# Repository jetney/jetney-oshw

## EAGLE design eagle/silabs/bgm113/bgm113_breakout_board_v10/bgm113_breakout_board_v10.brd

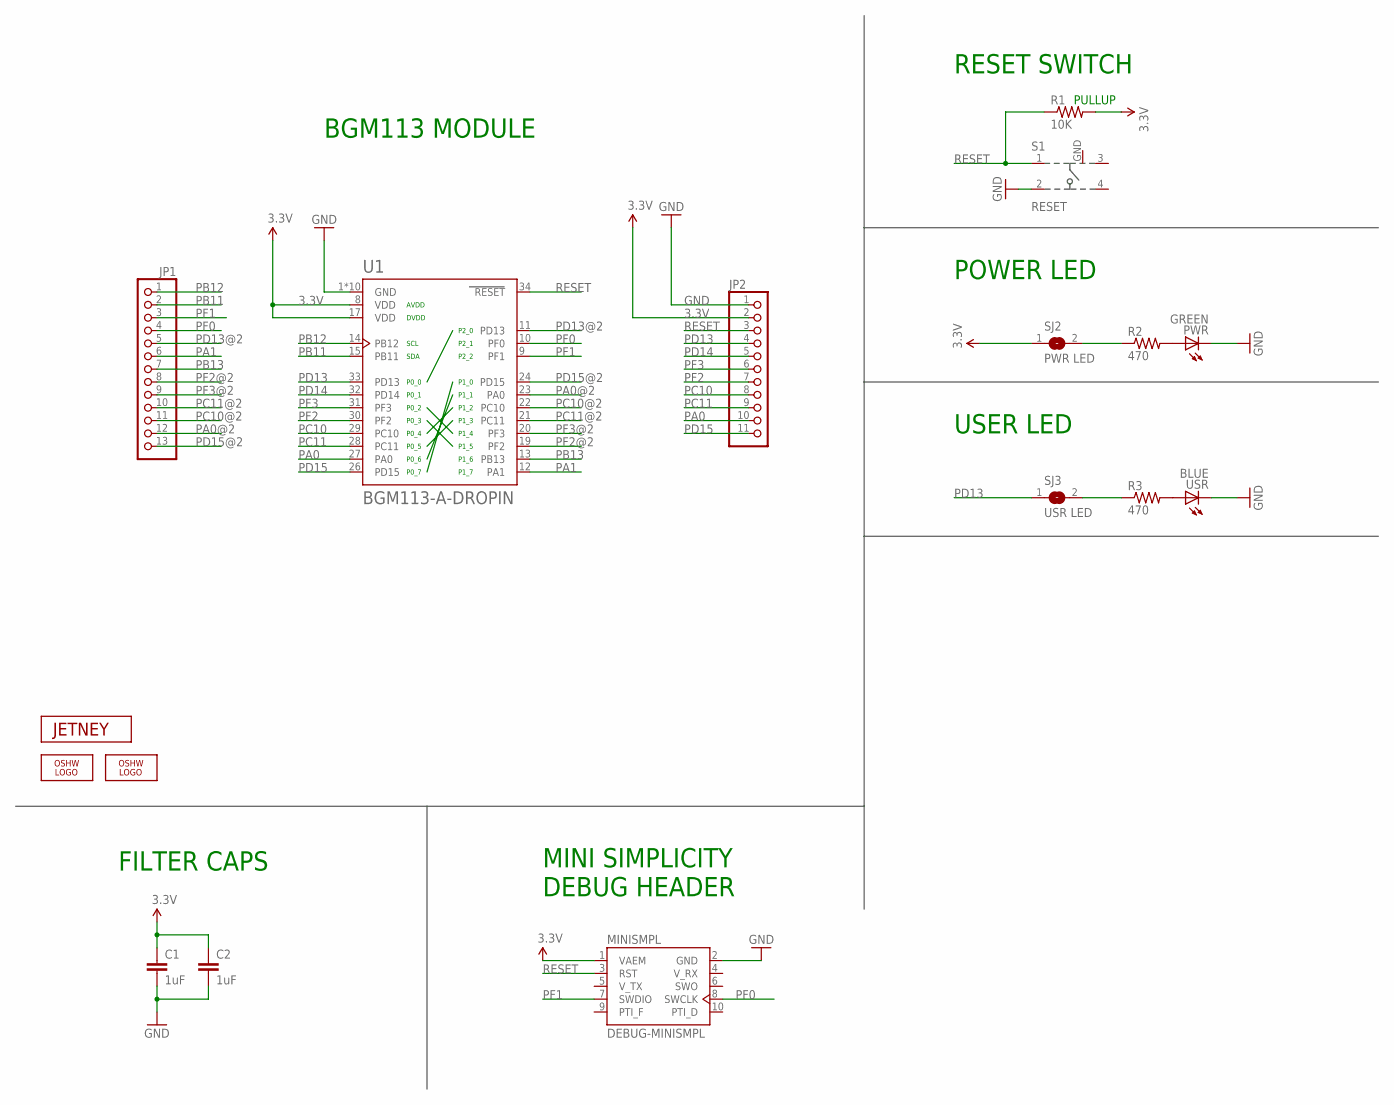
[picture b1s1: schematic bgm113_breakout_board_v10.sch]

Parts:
C1, C2: 1uF; 0603-CAP
JP1: PINHD-1X13; 1X13
JP2: PINHD-1X11; 1X11
LOGO1: OSHW_LOGO_FILLX0100-NT; OSHW_FILLX100_NOTEXT
LOGO2: OSHW_LOGO_FILLX0070-NT; OSHW_FILLX70_NOTEXT
MINISMPL: DEBUG-MINISMPL; DEBUG-50MIL
PWR: GREEN; CHIPLED_0805
R1: 10K; 0603-RES
R2, R3: 470; R0603
S1: RESET; 101-IG
SJ2: PWR LED; SJ
SJ3: USR LED; SJ
U1: BGM113-A-DROPIN; BLE113-A
U$2: JETNEY-LOGO-12
USR: BLUE; CHIPLED_0805

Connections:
3.3V: C1.1, C2.1, JP2.2, MINISMPL.1 (VAEM), R1.2, SJ2.1, U1.8 (VDD), U1.17 (VDD)
GND: C1.2, C2.2, JP2.1, MINISMPL.2 (GND), PWR.C, S1.2, S1.GND, U1.1 (GND), U1.2 (GND), U1.3 (GND), U1.4 (GND), U1.5 (GND), U1.6 (GND), U1.7 (GND), U1.18 (GND), U1.25 (GND), U1.36 (GND), USR.C
unnamed: PWR.A, R2.2
unnamed: R2.1, SJ2.2
unnamed: R3.2, USR.A
unnamed: R3.1, SJ3.2
PA0: JP2.10, U1.27 (PA0)
PA0@2: JP1.12, U1.23 (PA0)
PA1: JP1.6, U1.12 (PA1)
PB11: JP1.2, U1.15 (PB11)
PB12: JP1.1, U1.14 (PB12)
PB13: JP1.7, U1.13 (PB13)
PC10: JP2.8, U1.29 (PC10)
PC10@2: JP1.11, U1.22 (PC10)
PC11: JP2.9, U1.28 (PC11)
PC11@2: JP1.10, U1.21 (PC11)
PD13: JP2.4, SJ3.1, U1.33 (PD13)
PD13@2: JP1.5, U1.11 (PD13)
PD14: JP2.5, U1.32 (PD14)
PD15: JP2.11, U1.26 (PD15)
PD15@2: JP1.13, U1.24 (PD15)
PF0: JP1.4, MINISMPL.8 (SWCLK), U1.10 (PF0)
PF1: JP1.3, MINISMPL.7 (SWDIO), U1.9 (PF1)
PF2: JP2.7, U1.30 (PF2)
PF2@2: JP1.8, U1.19 (PF2)
PF3: JP2.6, U1.31 (PF3)
PF3@2: JP1.9, U1.20 (PF3)
RESET: JP2.3, MINISMPL.3 (RST), R1.1, S1.1, U1.34 (RESET)

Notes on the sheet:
POWER LED
USER LED
MINI SIMPLICITY DEBUG HEADER
BGM113 MODULE
RESET SWITCH
PULLUP
FILTER CAPS

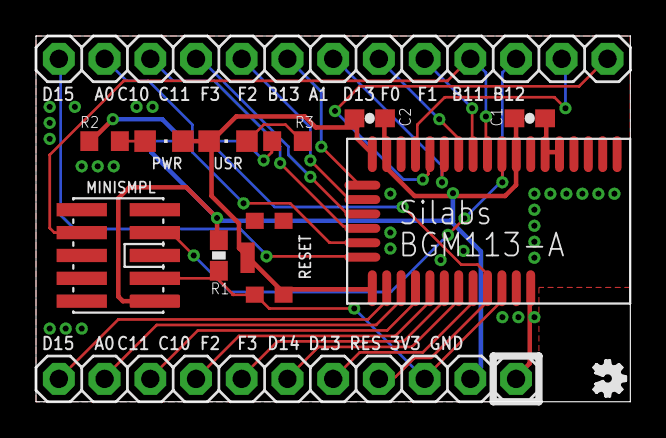
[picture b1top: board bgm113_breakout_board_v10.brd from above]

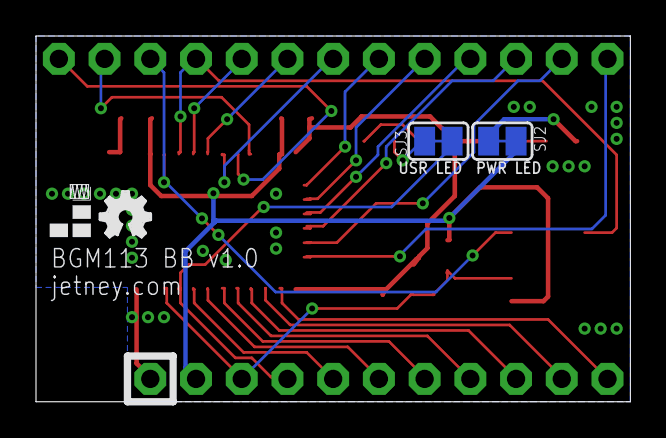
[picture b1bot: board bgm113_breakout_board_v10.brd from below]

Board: 2 copper layers, 33.0 x 20.3 mm, 17 parts (4 on the bottom side), 28 nets.

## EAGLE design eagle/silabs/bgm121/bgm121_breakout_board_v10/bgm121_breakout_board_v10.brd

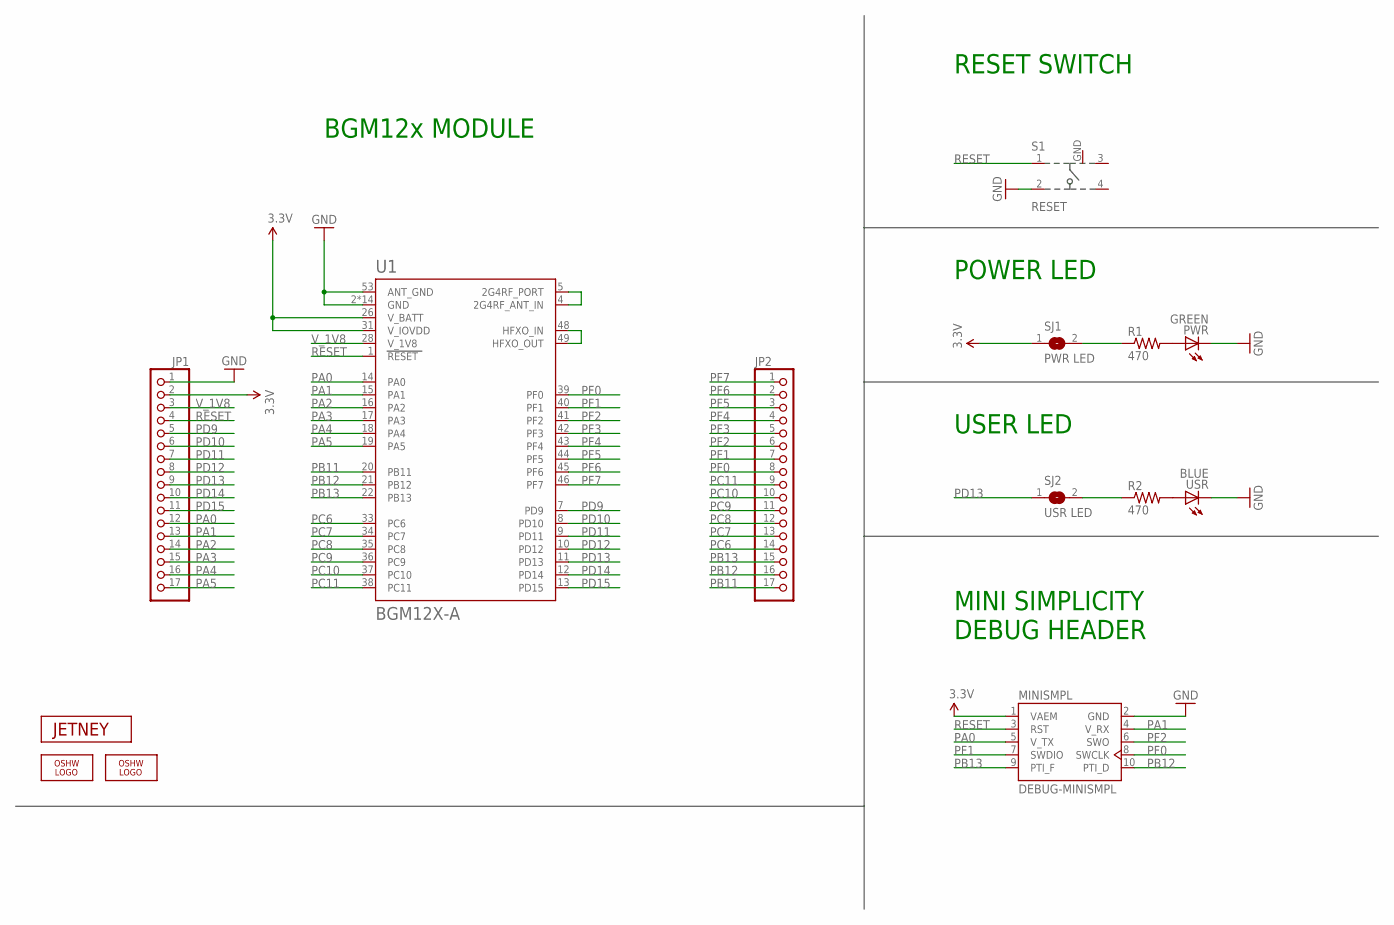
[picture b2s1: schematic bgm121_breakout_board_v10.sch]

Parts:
JP1, JP2: PINHD-1X17; 1X17
LOGO1: OSHW_LOGO_FILLX0100-NT; OSHW_FILLX100_NOTEXT
LOGO2: OSHW_LOGO_FILLX0070-NT; OSHW_FILLX70_NOTEXT
MINISMPL: DEBUG-MINISMPL; DEBUG-50MIL
PWR: GREEN; CHIPLED_0805
R1, R2: 470; R0603
S1: RESET; 101-IG
SJ1: PWR LED; SJ
SJ2: USR LED; SJ
U1: BGM12X-A
U$2: JETNEY-LOGO-12
USR: BLUE; CHIPLED_0805

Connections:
2G4RF: U1.4 (2G4RF_ANT_IN), U1.5 (2G4RF_PORT)
3.3V: JP1.2, MINISMPL.1 (VAEM), SJ1.1, U1.26 (V_BATT), U1.31 (V_IOVDD)
GND: JP1.1, MINISMPL.2 (GND), PWR.C, S1.2, S1.GND, U1.2 (GND), U1.3 (GND), U1.6 (GND), U1.25 (GND), U1.27 (GND), U1.29 (GND), U1.32 (GND), U1.47 (GND), U1.50 (GND), U1.51 (GND), U1.52 (GND), U1.53 (ANT_GND), U1.54 (GND), U1.55 (GND), U1.56 (GND), USR.C
HFXO: U1.48 (HFXO_IN), U1.49 (HFXO_OUT)
unnamed: PWR.A, R1.2
unnamed: R1.1, SJ1.2
unnamed: R2.2, USR.A
unnamed: R2.1, SJ2.2
PA0: JP1.12, MINISMPL.5 (V_TX), U1.14 (PA0)
PA1: JP1.13, MINISMPL.4 (V_RX), U1.15 (PA1)
PA2: JP1.14, U1.16 (PA2)
PA3: JP1.15, U1.17 (PA3)
PA4: JP1.16, U1.18 (PA4)
PA5: JP1.17, U1.19 (PA5)
PB11: JP2.17, U1.20 (PB11)
PB12: JP2.16, MINISMPL.10 (PTI_D), U1.21 (PB12)
PB13: JP2.15, MINISMPL.9 (PTI_F), U1.22 (PB13)
PC6: JP2.14, U1.33 (PC6)
PC7: JP2.13, U1.34 (PC7)
PC8: JP2.12, U1.35 (PC8)
PC9: JP2.11, U1.36 (PC9)
PC10: JP2.10, U1.37 (PC10)
PC11: JP2.9, U1.38 (PC11)
PD9: JP1.5, U1.7 (PD9)
PD10: JP1.6, U1.8 (PD10)
PD11: JP1.7, U1.9 (PD11)
PD12: JP1.8, U1.10 (PD12)
PD13: JP1.9, SJ2.1, U1.11 (PD13)
PD14: JP1.10, U1.12 (PD14)
PD15: JP1.11, U1.13 (PD15)
PF0: JP2.8, MINISMPL.8 (SWCLK), U1.39 (PF0)
PF1: JP2.7, MINISMPL.7 (SWDIO), U1.40 (PF1)
PF2: JP2.6, MINISMPL.6 (SWO), U1.41 (PF2)
PF3: JP2.5, U1.42 (PF3)
PF4: JP2.4, U1.43 (PF4)
PF5: JP2.3, U1.44 (PF5)
PF6: JP2.2, U1.45 (PF6)
PF7: JP2.1, U1.46 (PF7)
RESET: JP1.4, MINISMPL.3 (RST), S1.1, U1.1 (RESET)
V_1V8: JP1.3, U1.28 (V_1V8)

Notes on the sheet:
POWER LED
USER LED
MINI SIMPLICITY DEBUG HEADER
BGM12x MODULE
RESET SWITCH

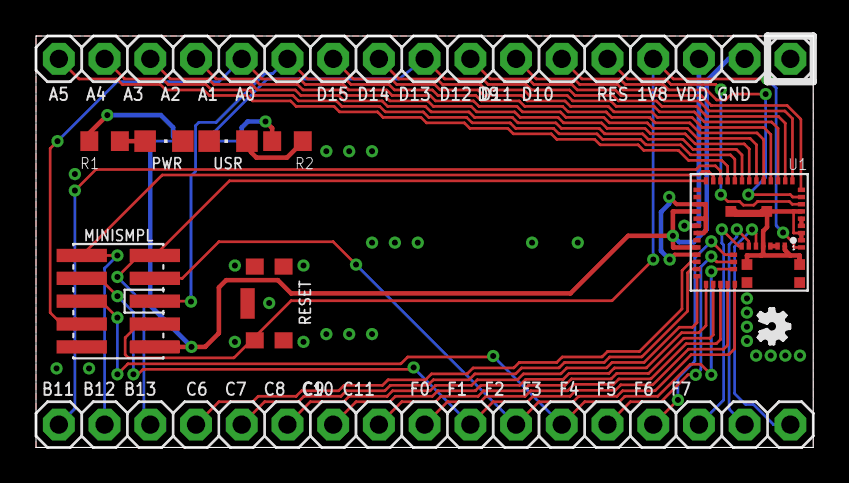
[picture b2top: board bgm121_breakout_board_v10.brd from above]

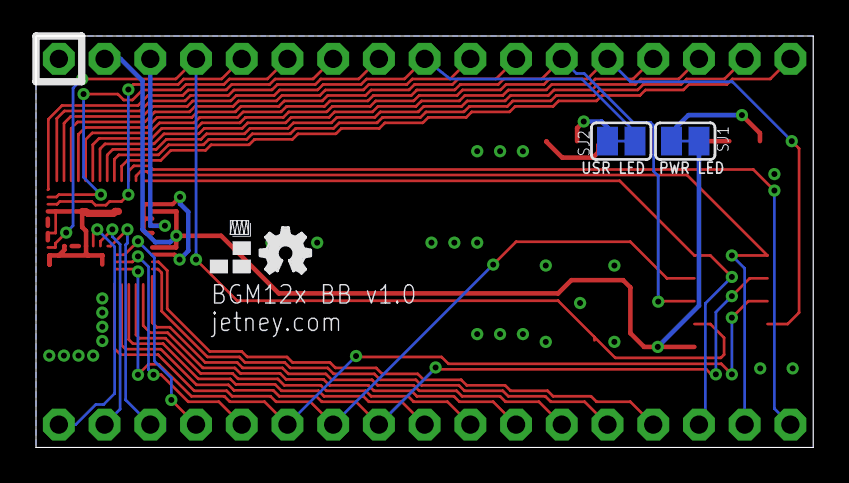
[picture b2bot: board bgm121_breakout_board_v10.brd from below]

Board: 2 copper layers, 43.2 x 22.9 mm, 14 parts (4 on the bottom side), 40 nets.

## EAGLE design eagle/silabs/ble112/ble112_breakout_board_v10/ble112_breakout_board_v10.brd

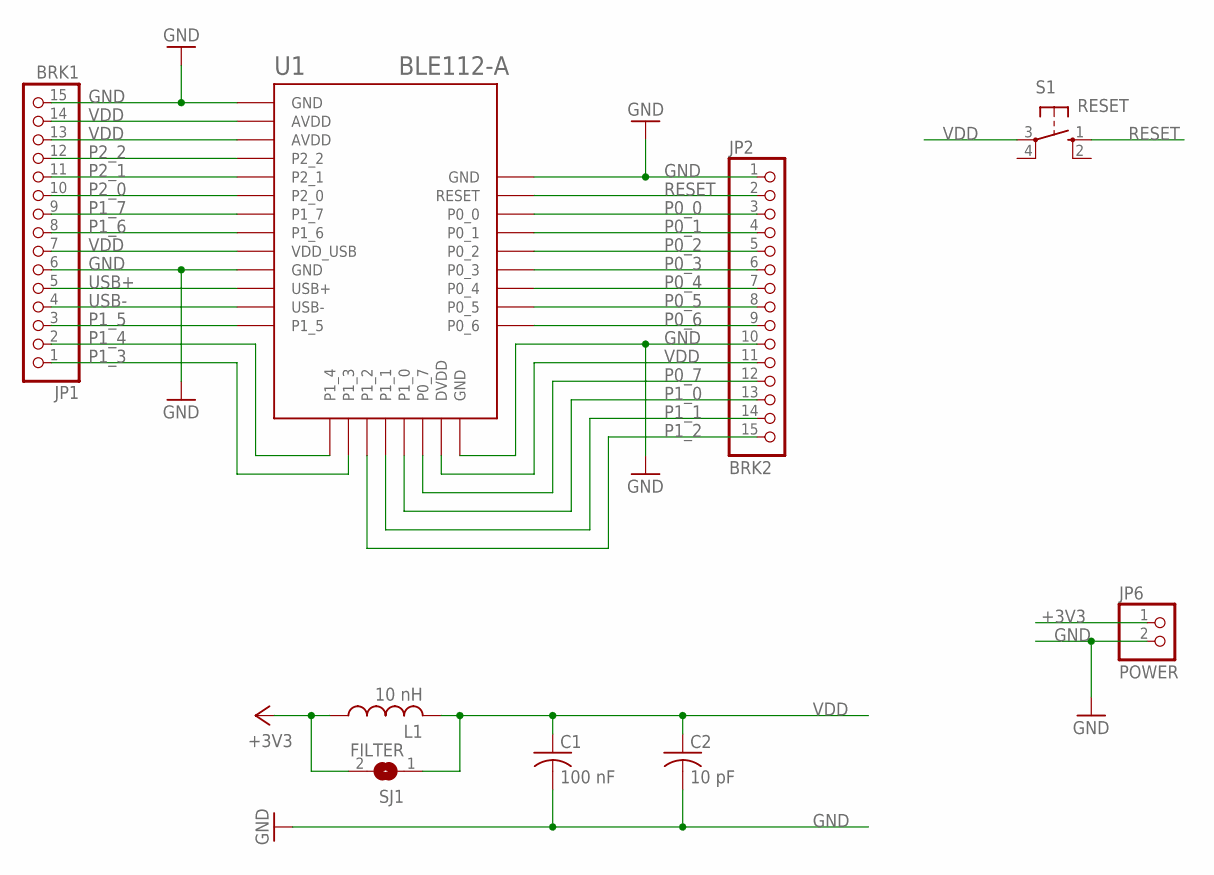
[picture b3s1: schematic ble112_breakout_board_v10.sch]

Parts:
C1: 100 nF; C025-025X050
C2: 10 pF; C025-025X050
JP1: BRK1; 1X15
JP2: BRK2; 1X15
JP6: POWER; 1X02
L1: 10 nH; 0204/7
S1: RESET; B3F-10XX
SJ1: FILTER; SJ
U1: BLE112-A

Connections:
+3V3: JP6.1, L1.1, SJ1.2
GND: C1.2, C2.2, JP1.6, JP1.15, JP2.1, JP2.10, JP6.2, U1.GND1 (GND), U1.GND2 (GND), U1.GND3 (GND), U1.GND4 (GND)
P0_0: JP2.3, U1.P0_0
P0_1: JP2.4, U1.P0_1
P0_2: JP2.5, U1.P0_2
P0_3: JP2.6, U1.P0_3
P0_4: JP2.7, U1.P0_4
P0_5: JP2.8, U1.P0_5
P0_6: JP2.9, U1.P0_6
P0_7: JP2.12, U1.P0_7
P1_0: JP2.13, U1.P1_0
P1_1: JP2.14, U1.P1_1
P1_2: JP2.15, U1.P1_2
P1_3: JP1.1, U1.P1_3
P1_4: JP1.2, U1.P1_4
P1_5: JP1.3, U1.P1_5
P1_6: JP1.8, U1.P1_6
P1_7: JP1.9, U1.P1_7
P2_0: JP1.10, U1.P2_0
P2_1: JP1.11, U1.P2_1
P2_2: JP1.12, U1.P2_2
RESET: JP2.2, S1.1 (S), U1.RESET
USB+: JP1.5, U1.USB+
USB-: JP1.4, U1.USB-
VDD: C1.1, C2.1, JP1.7, JP1.13, JP1.14, JP2.11, L1.2, S1.3, SJ1.1, U1.AVDD1 (AVDD), U1.AVDD2 (AVDD), U1.DVDD, U1.VDD_USB

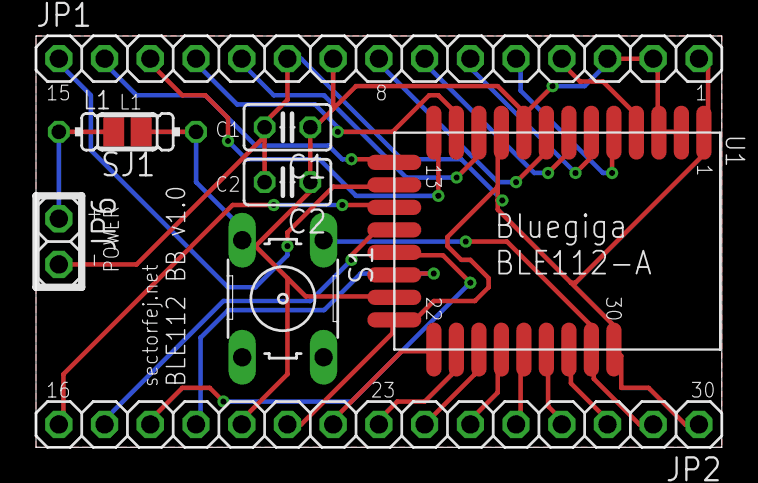
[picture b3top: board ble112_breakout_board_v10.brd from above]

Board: 2 copper layers, 38.1 x 22.9 mm, 9 parts (0 on the bottom side), 25 nets.

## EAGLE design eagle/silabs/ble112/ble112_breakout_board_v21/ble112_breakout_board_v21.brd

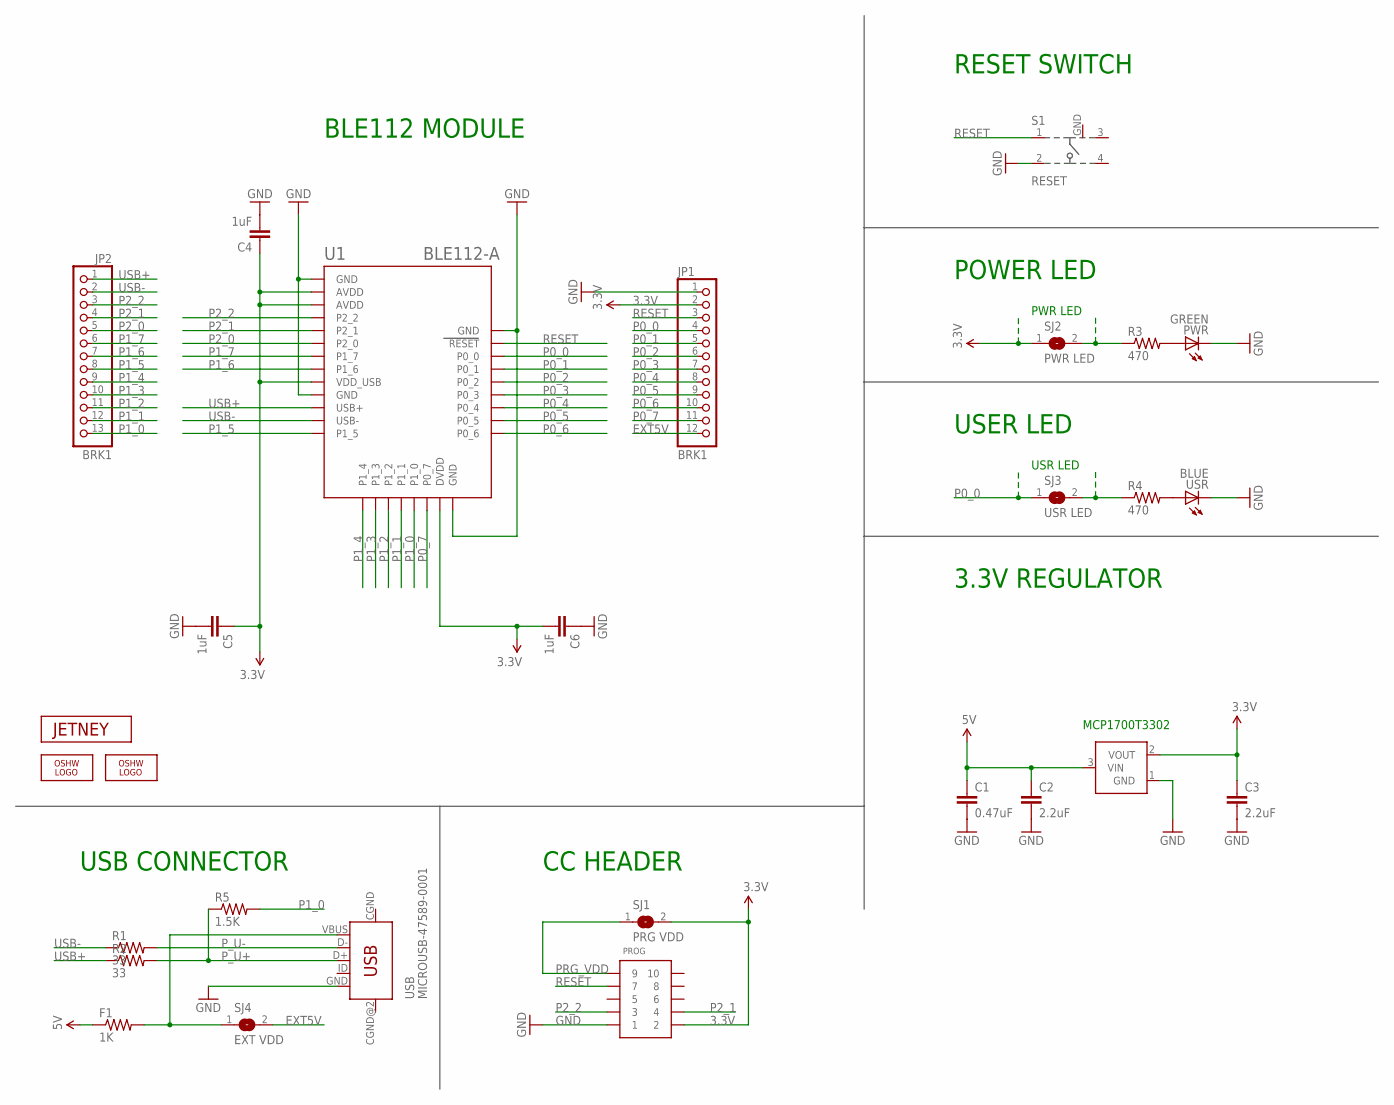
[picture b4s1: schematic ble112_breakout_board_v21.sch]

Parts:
C1: 0.47uF; 0603-CAP
C2, C3: 2.2uF; 0603-CAP
C4, C5, C6: 1uF; 0603-CAP
F1: 1K; 0805
JP1: BRK1; 1X12
JP2: BRK1; 1X13
LOGO1, LOGO2: OSHW_LOGO_FILLX0100-NT; OSHW_FILLX100_NOTEXT
PROG: CONN_5-2-FTSH-V; FTSH-105-DV
PWR: GREEN; CHIPLED_0805
R1, R2: 33; 0603-RES
R3, R4: 470; R0603
R5: 1.5K; 0603-RES
S1: RESET; 101-IG
SJ1: PRG VDD; SJ
SJ2: PWR LED; SJ
SJ3: USR LED; SJ
SJ4: EXT VDD; SJ
U1: BLE112-A
U2: MCP1700; SOT23-3
U$3: JETNEY-LOGO-12
USB: MICROUSB-47589-0001
USR: BLUE; CHIPLED_0805

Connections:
3.3V: C3.1, C4.1, C5.1, C6.2, JP1.2, PROG.2, SJ1.2, SJ2.1, U1.AVDD, U1.AVDD@2 (AVDD), U1.DVDD, U1.VDD_USB, U2.2 (VOUT)
5V: C1.1, C2.1, F1.1, U2.3 (VIN)
EXT5V: JP1.12, SJ4.2
GND: C1.2, C2.2, C3.2, C4.2, C5.2, C6.1, JP1.1, PROG.1, PWR.C, S1.2, S1.GND, U1.GND, U1.GND@2 (GND), U1.GND@3 (GND), U1.GND@4 (GND), U2.1 (GND), USB.GND, USR.C
unnamed: PWR.A, R3.2
unnamed: R3.1, SJ2.2
unnamed: R4.2, USR.A
unnamed: R4.1, SJ3.2
P0_0: JP1.4, SJ3.1, U1.P0_0
P0_1: JP1.5, U1.P0_1
P0_2: JP1.6, U1.P0_2
P0_3: JP1.7, U1.P0_3
P0_4: JP1.8, U1.P0_4
P0_5: JP1.9, U1.P0_5
P0_6: JP1.10, U1.P0_6
P0_7: JP1.11, U1.P0_7
P1_0: JP2.13, R5.2, U1.P1_0
P1_1: JP2.12, U1.P1_1
P1_2: JP2.11, U1.P1_2
P1_3: JP2.10, U1.P1_3
P1_4: JP2.9, U1.P1_4
P1_5: JP2.8, U1.P1_5
P1_6: JP2.7, U1.P1_6
P1_7: JP2.6, U1.P1_7
P2_0: JP2.5, U1.P2_0
P2_1: JP2.4, PROG.4, U1.P2_1
P2_2: JP2.3, PROG.3, U1.P2_2
PRG_VDD: PROG.9, SJ1.1
P_U+: R2.2, R5.1, USB.D+
P_U-: R1.2, USB.D-
RESET: JP1.3, PROG.7, S1.1, U1.RESET
USB+: JP2.1, R2.1, U1.USB+
USB-: JP2.2, R1.1, U1.USB-
VBUS: F1.2, SJ4.1, USB.VBUS

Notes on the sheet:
PWR LED
USR LED
POWER LED
USER LED
USB CONNECTOR
CC HEADER
BLE112 MODULE
3.3V REGULATOR
RESET SWITCH
MCP1700T3302

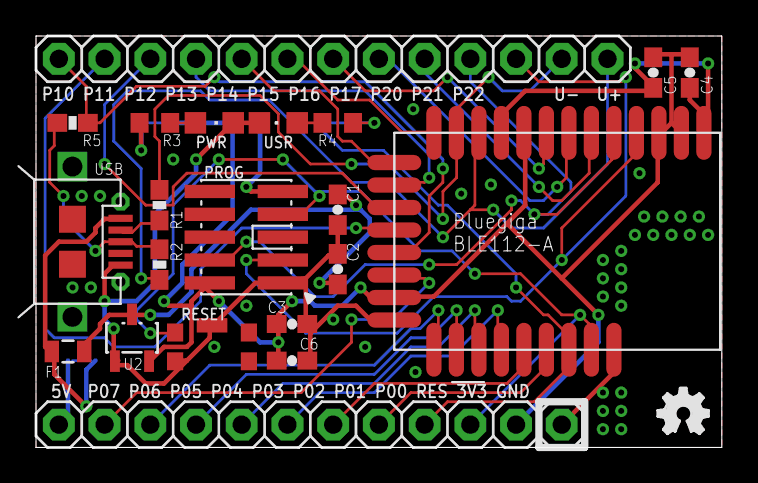
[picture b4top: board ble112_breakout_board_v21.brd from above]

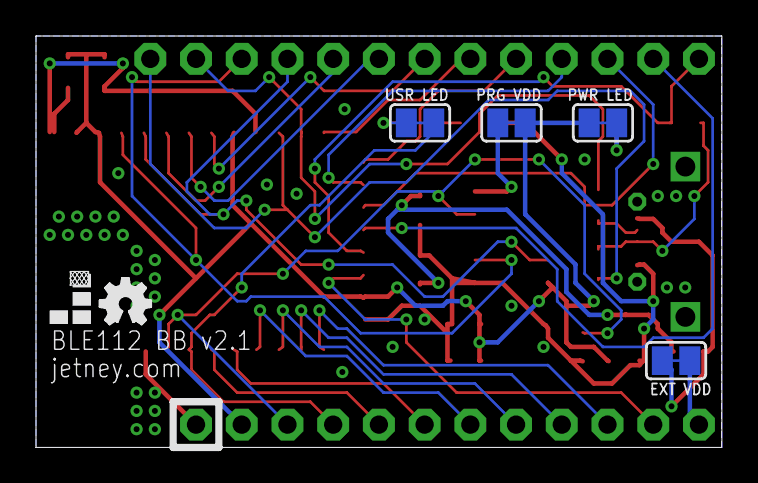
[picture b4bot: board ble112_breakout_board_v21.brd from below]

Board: 2 copper layers, 38.1 x 22.9 mm, 28 parts (6 on the bottom side), 34 nets.

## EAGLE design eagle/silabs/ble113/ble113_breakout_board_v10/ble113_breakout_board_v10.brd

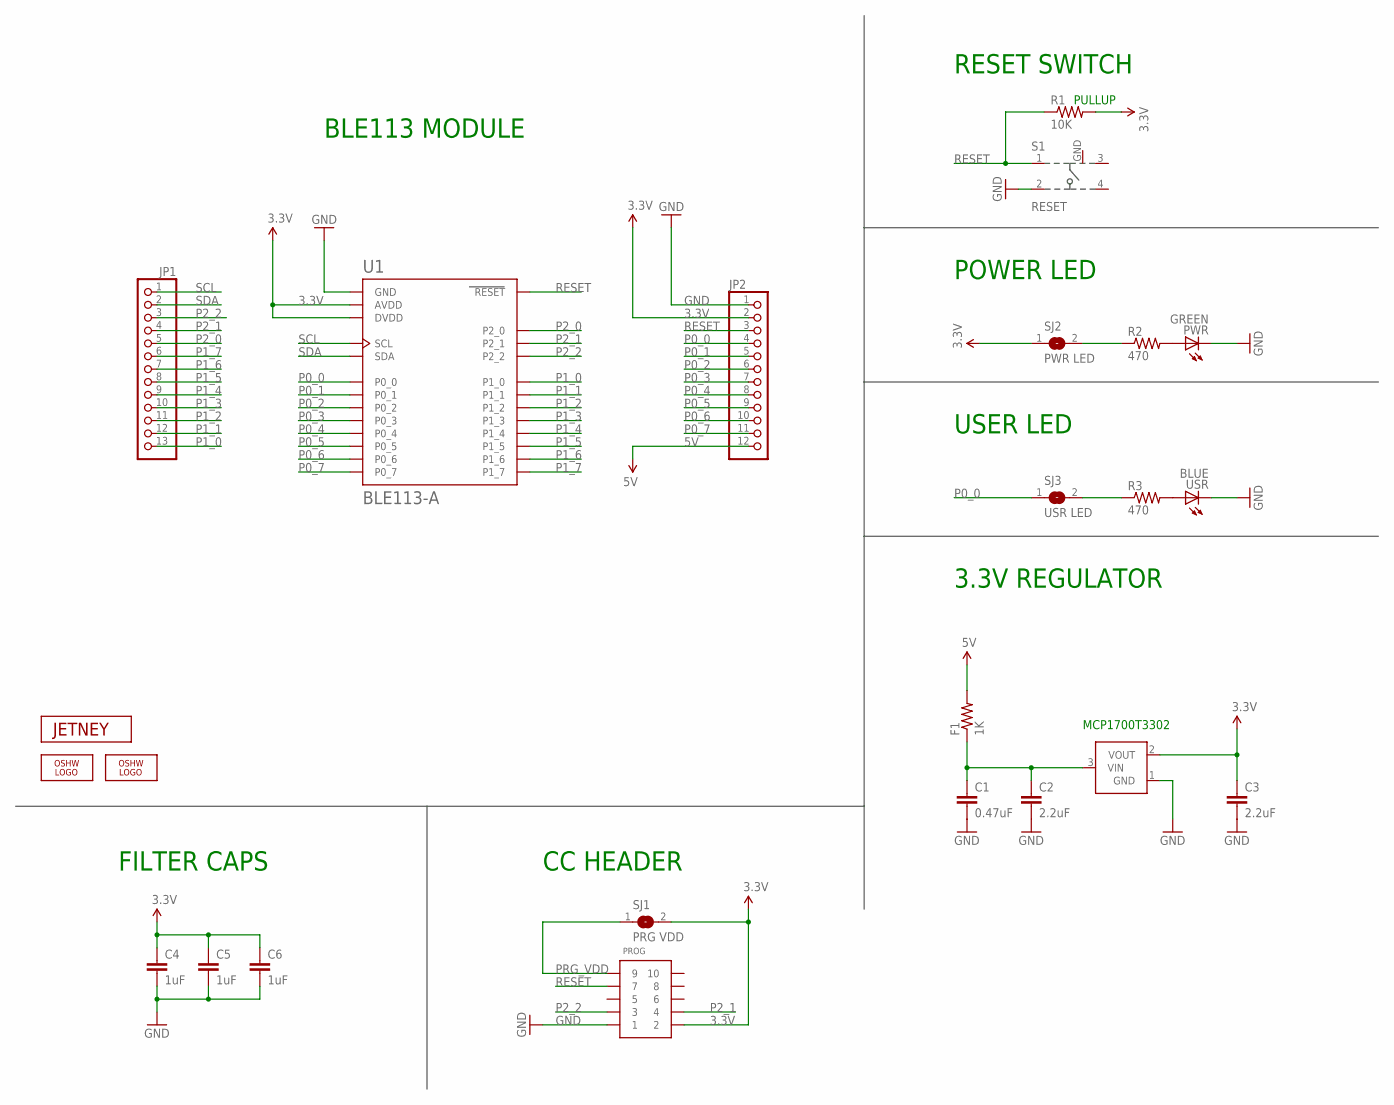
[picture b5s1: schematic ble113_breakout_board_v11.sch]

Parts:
C1: 0.47uF; 0603-CAP
C2, C3: 2.2uF; 0603-CAP
C4, C5, C6: 1uF; 0603-CAP
F1: 1K; 0805
JP1: PINHD-1X13; 1X13
JP2: PINHD-1X12; 1X12
LOGO1: OSHW_LOGO_FILLX0100-NT; OSHW_FILLX100_NOTEXT
LOGO2: OSHW_LOGO_FILLX0070-NT; OSHW_FILLX70_NOTEXT
PROG: CONN_5-2-FTSH-V; FTSH-105-DV
PWR: GREEN; CHIPLED_0805
R1: 10K; 0603-RES
R2, R3: 470; R0603
S1: RESET; 101-IG
SJ1: PRG VDD; SJ
SJ2: PWR LED; SJ
SJ3: USR LED; SJ
U1: BLE113-A
U2: MCP1700; SOT23-3
U$2: JETNEY-LOGO-12
USR: BLUE; CHIPLED_0805

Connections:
5V: F1.2, JP2.12
GND: C1.2, C2.2, C3.2, C4.2, C5.2, C6.2, JP2.1, PROG.1, PWR.C, S1.2, S1.GND, U1.GND, U1.GND@2 (GND), U1.GND@3 (GND), U1.GND@4 (GND), U1.GND@5 (GND), U1.GND@6 (GND), U1.GND@7 (GND), U1.GND@8 (GND), U1.GND@9 (GND), U1.GND@10 (GND), U2.1 (GND), USR.C
unnamed: PWR.A, R2.2
unnamed: R2.1, SJ2.2
unnamed: R3.2, USR.A
unnamed: R3.1, SJ3.2
P0_0: JP2.4, SJ3.1, U1.P0_0
P0_1: JP2.5, U1.P0_1
P0_2: JP2.6, U1.P0_2
P0_3: JP2.7, U1.P0_3
P0_4: JP2.8, U1.P0_4
P0_5: JP2.9, U1.P0_5
P0_6: JP2.10, U1.P0_6
P0_7: JP2.11, U1.P0_7
P1_0: JP1.13, U1.P1_0
P1_1: JP1.12, U1.P1_1
P1_2: JP1.11, U1.P1_2
P1_3: JP1.10, U1.P1_3
P1_4: JP1.9, U1.P1_4
P1_5: JP1.8, U1.P1_5
P1_6: JP1.7, U1.P1_6
P1_7: JP1.6, U1.P1_7
P2_0: JP1.5, U1.P2_0
P2_1: JP1.4, PROG.4, U1.P2_1
P2_2: JP1.3, PROG.3, U1.P2_2
PRG_VDD: PROG.9, SJ1.1
RESET: JP2.3, PROG.7, R1.1, S1.1, U1.RESET
SCL: JP1.1, U1.SCL
SDA: JP1.2, U1.SDA

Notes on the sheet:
POWER LED
USER LED
CC HEADER
BLE113 MODULE
3.3V REGULATOR
RESET SWITCH
PULLUP
MCP1700T3302
FILTER CAPS

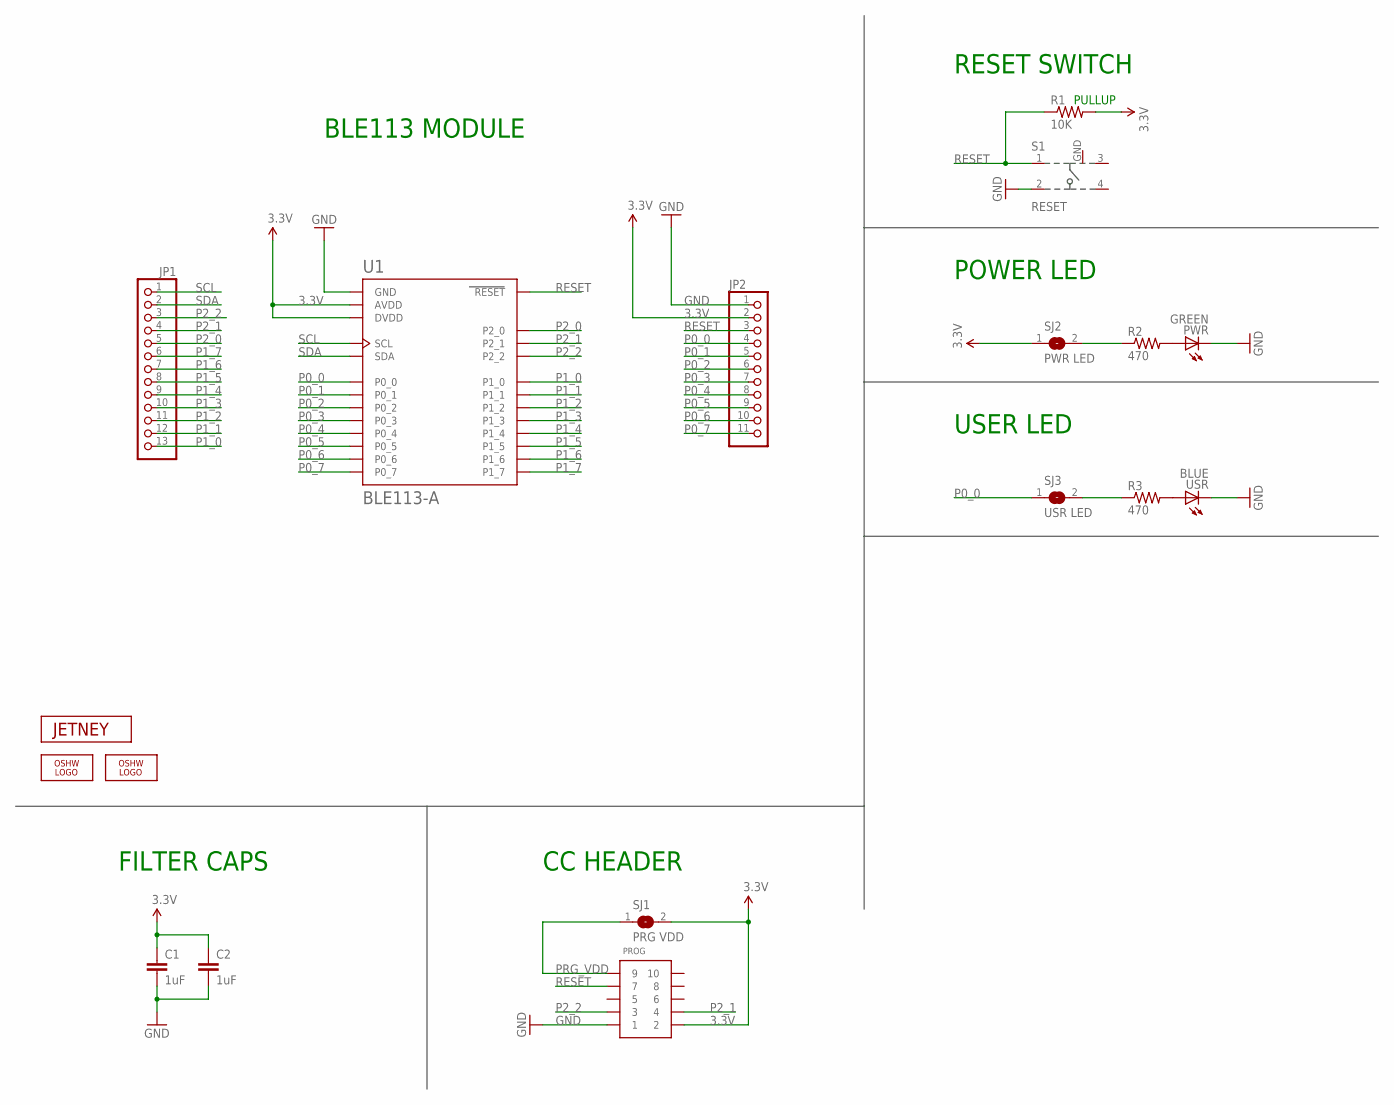
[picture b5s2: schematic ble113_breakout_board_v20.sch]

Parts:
C1, C2: 1uF; 0603-CAP
JP1: PINHD-1X13; 1X13
JP2: PINHD-1X11; 1X11
LOGO1: OSHW_LOGO_FILLX0100-NT; OSHW_FILLX100_NOTEXT
LOGO2: OSHW_LOGO_FILLX0070-NT; OSHW_FILLX70_NOTEXT
PROG: CONN_5-2-FTSH-V; FTSH-105-DV
PWR: GREEN; CHIPLED_0805
R1: 10K; 0603-RES
R2, R3: 470; R0603
S1: RESET; 101-IG
SJ1: PRG VDD; SJ
SJ2: PWR LED; SJ
SJ3: USR LED; SJ
U1: BLE113-A
U$2: JETNEY-LOGO-12
USR: BLUE; CHIPLED_0805

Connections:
GND: C1.2, C2.2, JP2.1, PROG.1, PWR.C, S1.2, S1.GND, U1.GND, U1.GND@2 (GND), U1.GND@3 (GND), U1.GND@4 (GND), U1.GND@5 (GND), U1.GND@6 (GND), U1.GND@7 (GND), U1.GND@8 (GND), U1.GND@9 (GND), U1.GND@10 (GND), USR.C; also elsewhere on the board
unnamed: PWR.A, R2.2
unnamed: R2.1, SJ2.2
unnamed: R3.2, USR.A
unnamed: R3.1, SJ3.2
P0_0: JP2.4, SJ3.1, U1.P0_0
P0_1: JP2.5, U1.P0_1
P0_2: JP2.6, U1.P0_2
P0_3: JP2.7, U1.P0_3
P0_4: JP2.8, U1.P0_4
P0_5: JP2.9, U1.P0_5
P0_6: JP2.10, U1.P0_6
P0_7: JP2.11, U1.P0_7
P1_0: JP1.13, U1.P1_0
P1_1: JP1.12, U1.P1_1
P1_2: JP1.11, U1.P1_2
P1_3: JP1.10, U1.P1_3
P1_4: JP1.9, U1.P1_4
P1_5: JP1.8, U1.P1_5
P1_6: JP1.7, U1.P1_6
P1_7: JP1.6, U1.P1_7
P2_0: JP1.5, U1.P2_0
P2_1: JP1.4, PROG.4, U1.P2_1
P2_2: JP1.3, PROG.3, U1.P2_2
PRG_VDD: PROG.9, SJ1.1
RESET: JP2.3, PROG.7, R1.1, S1.1, U1.RESET
SCL: JP1.1, U1.SCL
SDA: JP1.2, U1.SDA

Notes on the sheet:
POWER LED
USER LED
CC HEADER
BLE113 MODULE
RESET SWITCH
PULLUP
FILTER CAPS

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
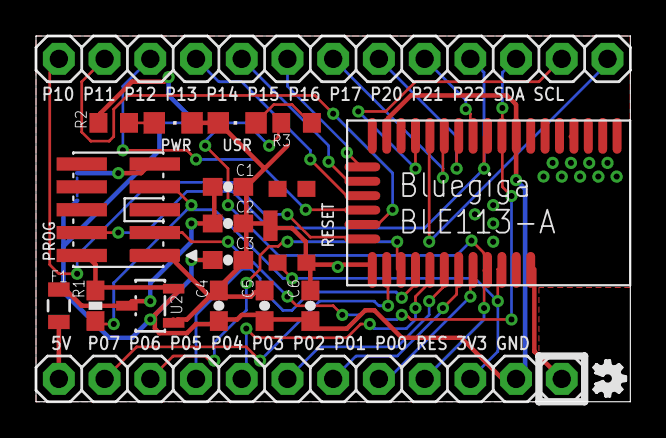
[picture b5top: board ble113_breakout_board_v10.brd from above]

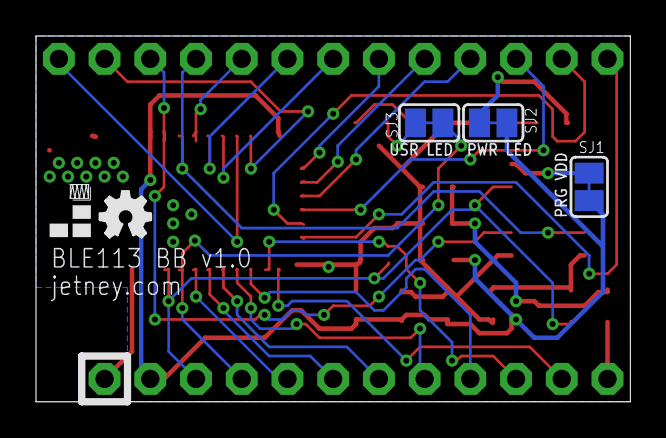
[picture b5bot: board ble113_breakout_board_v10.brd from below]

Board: 2 copper layers, 33.0 x 20.3 mm, 24 parts (5 on the bottom side), 31 nets.

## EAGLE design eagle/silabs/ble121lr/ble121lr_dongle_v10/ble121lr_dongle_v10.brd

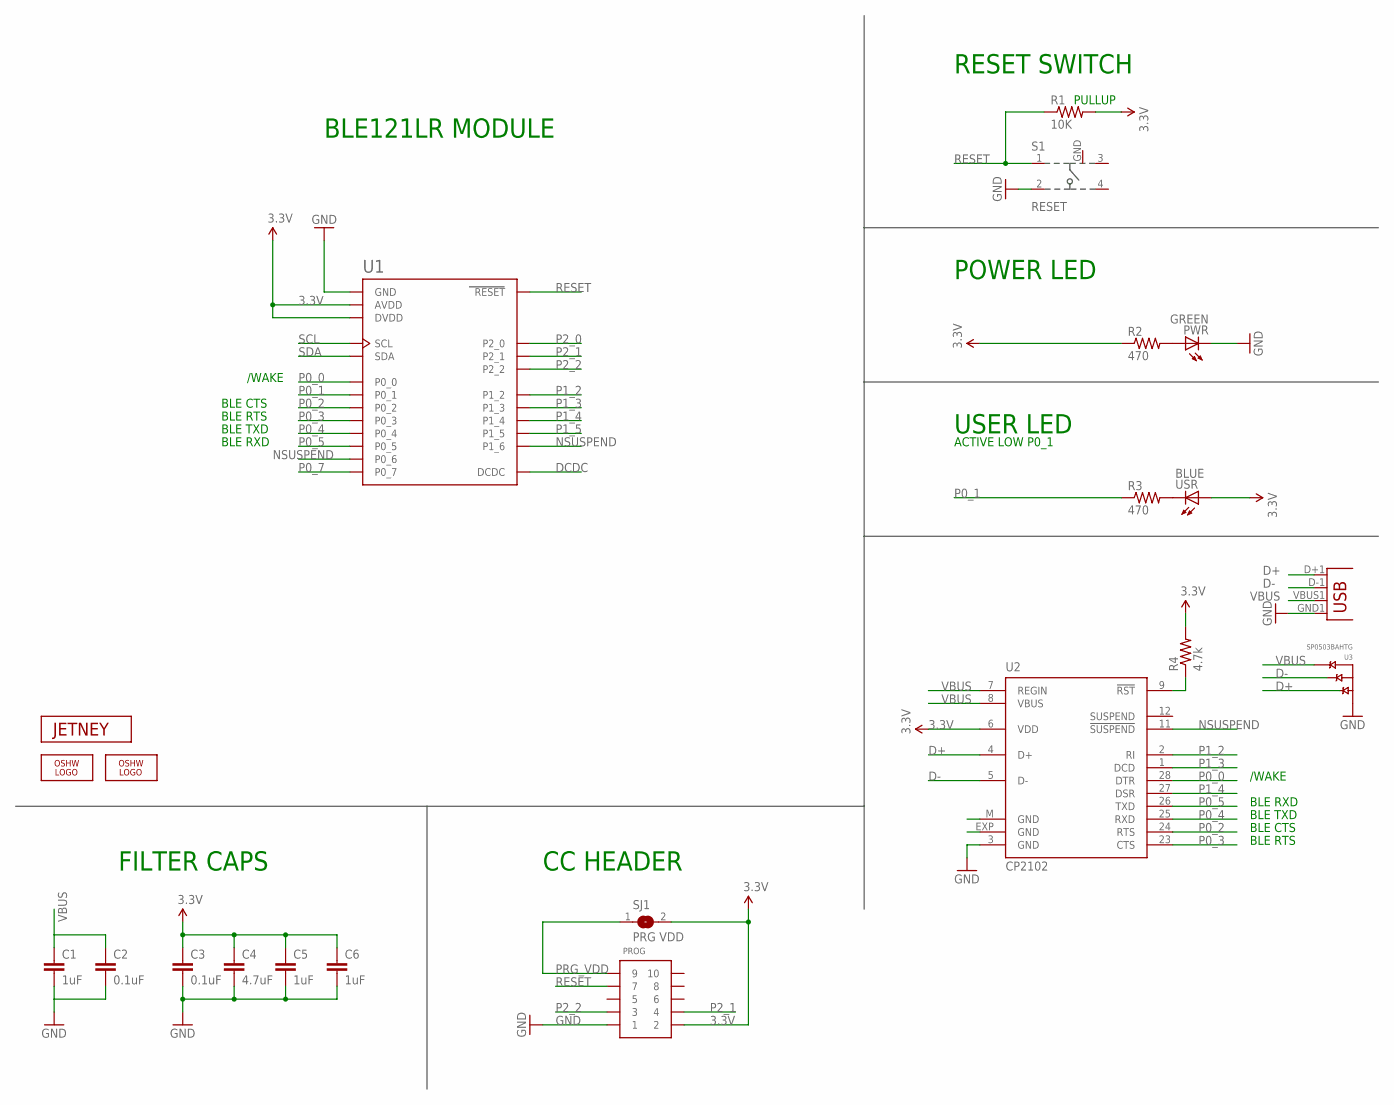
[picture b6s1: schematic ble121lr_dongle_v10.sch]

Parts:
C1, C5, C6: 1uF; 0603-CAP
C2, C3: 0.1uF; 0603-CAP
C4: 4.7uF; 0603-CAP
JP1: USBA-SMD-MALE; USB-A-SMT-MALE
LOGO1: OSHW_LOGO_FILLX0100-NT; OSHW_FILLX100_NOTEXT
LOGO2: OSHW_LOGO_FILLX0070-NT; OSHW_FILLX70_NOTEXT
PROG: CONN_5-2-FTSH-V; FTSH-105-DV
PWR: GREEN; CHIPLED_0805
R1: 10K; 0603-RES
R2, R3: 470; R0603
R4: 4.7k; R0603
S1: RESET; 101-IG
SJ1: PRG VDD; SJ
U1: BLE121LR-A
U2: CP2102; MLP28
U3: SP0503BAHTG; SOT143
U$2: JETNEY-LOGO-12
USR: BLUE; CHIPLED_0805

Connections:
3.3V: C3.1, C4.1, C5.1, C6.1, PROG.2, R1.2, R2.1, R4.2, SJ1.2, U1.AVDD, U1.DVDD, U2.6 (VDD), USR.A
D+: JP1.D+1 (D+), U2.4 (D+), U3.2 (A)
D-: JP1.D-1 (D-), U2.5 (D-), U3.3 (B)
DCDC: U1.DCDC
GND: C1.2, C2.2, C3.2, C4.2, C5.2, C6.2, JP1.GND1 (GND), PROG.1, PWR.C, S1.2, S1.GND, U1.GND, U1.GND@2 (GND), U1.GND@3 (GND), U1.GND@4 (GND), U1.GND@5 (GND), U1.GND@6 (GND), U1.GND@7 (GND), U1.GND@8 (GND), U1.GND@9 (GND), U1.GND@10 (GND), U1.GND@11 (GND), U1.GND@12 (GND), U1.GND@13 (GND), U2.3 (GND), U3.1 (GND)
unnamed: PWR.A, R2.2
unnamed: R3.2, USR.C
unnamed: R4.1, U2.9 (!RST)
NSUSPEND: U1.P0_6, U1.P1_6, U2.11 (!SUSPEND)
P0_0: U1.P0_0, U2.28 (DTR)
P0_1: R3.1, U1.P0_1
P0_2: U1.P0_2, U2.24 (RTS)
P0_3: U1.P0_3, U2.23 (CTS)
P0_4: U1.P0_4, U2.25 (RXD)
P0_5: U1.P0_5, U2.26 (TXD)
P0_7: U1.P0_7
P1_2: U1.P1_2, U2.2 (RI)
P1_3: U1.P1_3, U2.1 (DCD)
P1_4: U1.P1_4, U2.27 (DSR)
P1_5: U1.P1_5
P2_0: U1.P2_0
P2_1: PROG.4, U1.P2_1
P2_2: PROG.3, U1.P2_2
PRG_VDD: PROG.9, SJ1.1
RESET: PROG.7, R1.1, S1.1, U1.RESET
SCL: U1.SCL
SDA: U1.SDA
VBUS: C1.1, C2.1, JP1.VBUS1 (VBUS), U2.7 (REGIN), U2.8 (VBUS), U3.4 (C)

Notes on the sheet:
POWER LED
USER LED
CC HEADER
BLE121LR MODULE
RESET SWITCH
PULLUP
FILTER CAPS
BLE RXD
BLE TXD
BLE CTS
BLE RTS
/WAKE
ACTIVE LOW P0_1

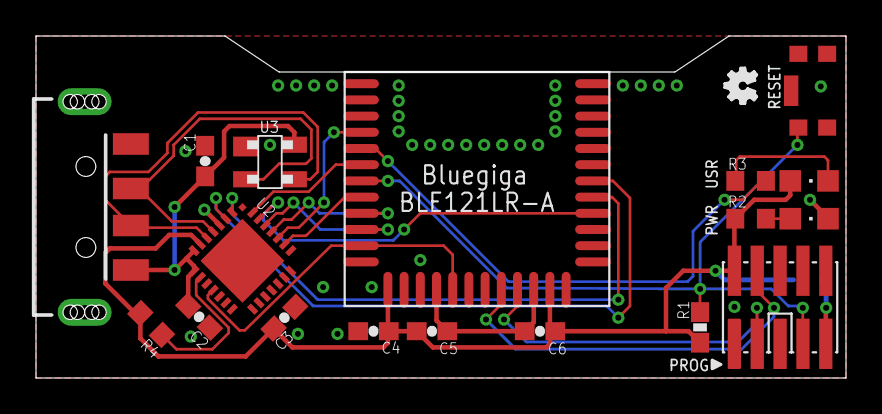
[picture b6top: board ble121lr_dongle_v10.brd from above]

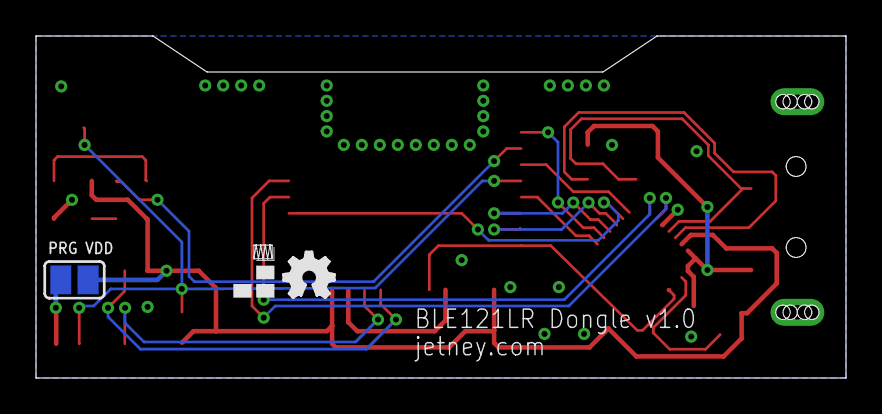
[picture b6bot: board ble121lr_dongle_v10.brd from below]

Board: 2 copper layers, 45.0 x 19.0 mm, 22 parts (3 on the bottom side), 22 nets.

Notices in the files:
parts and their libraries:
SparkFun: Licensing: CC v3.0 Share-Alike You are welcome to use this library for commercial purposes.
jetney-silabs-modules: Package design from "pretty-eagle-libs" at https://github.com/esden/pretty-eagle-libs/blob/master/pel_misc.lbr by @esden at Github. (CC-BY-SA-3.0)
